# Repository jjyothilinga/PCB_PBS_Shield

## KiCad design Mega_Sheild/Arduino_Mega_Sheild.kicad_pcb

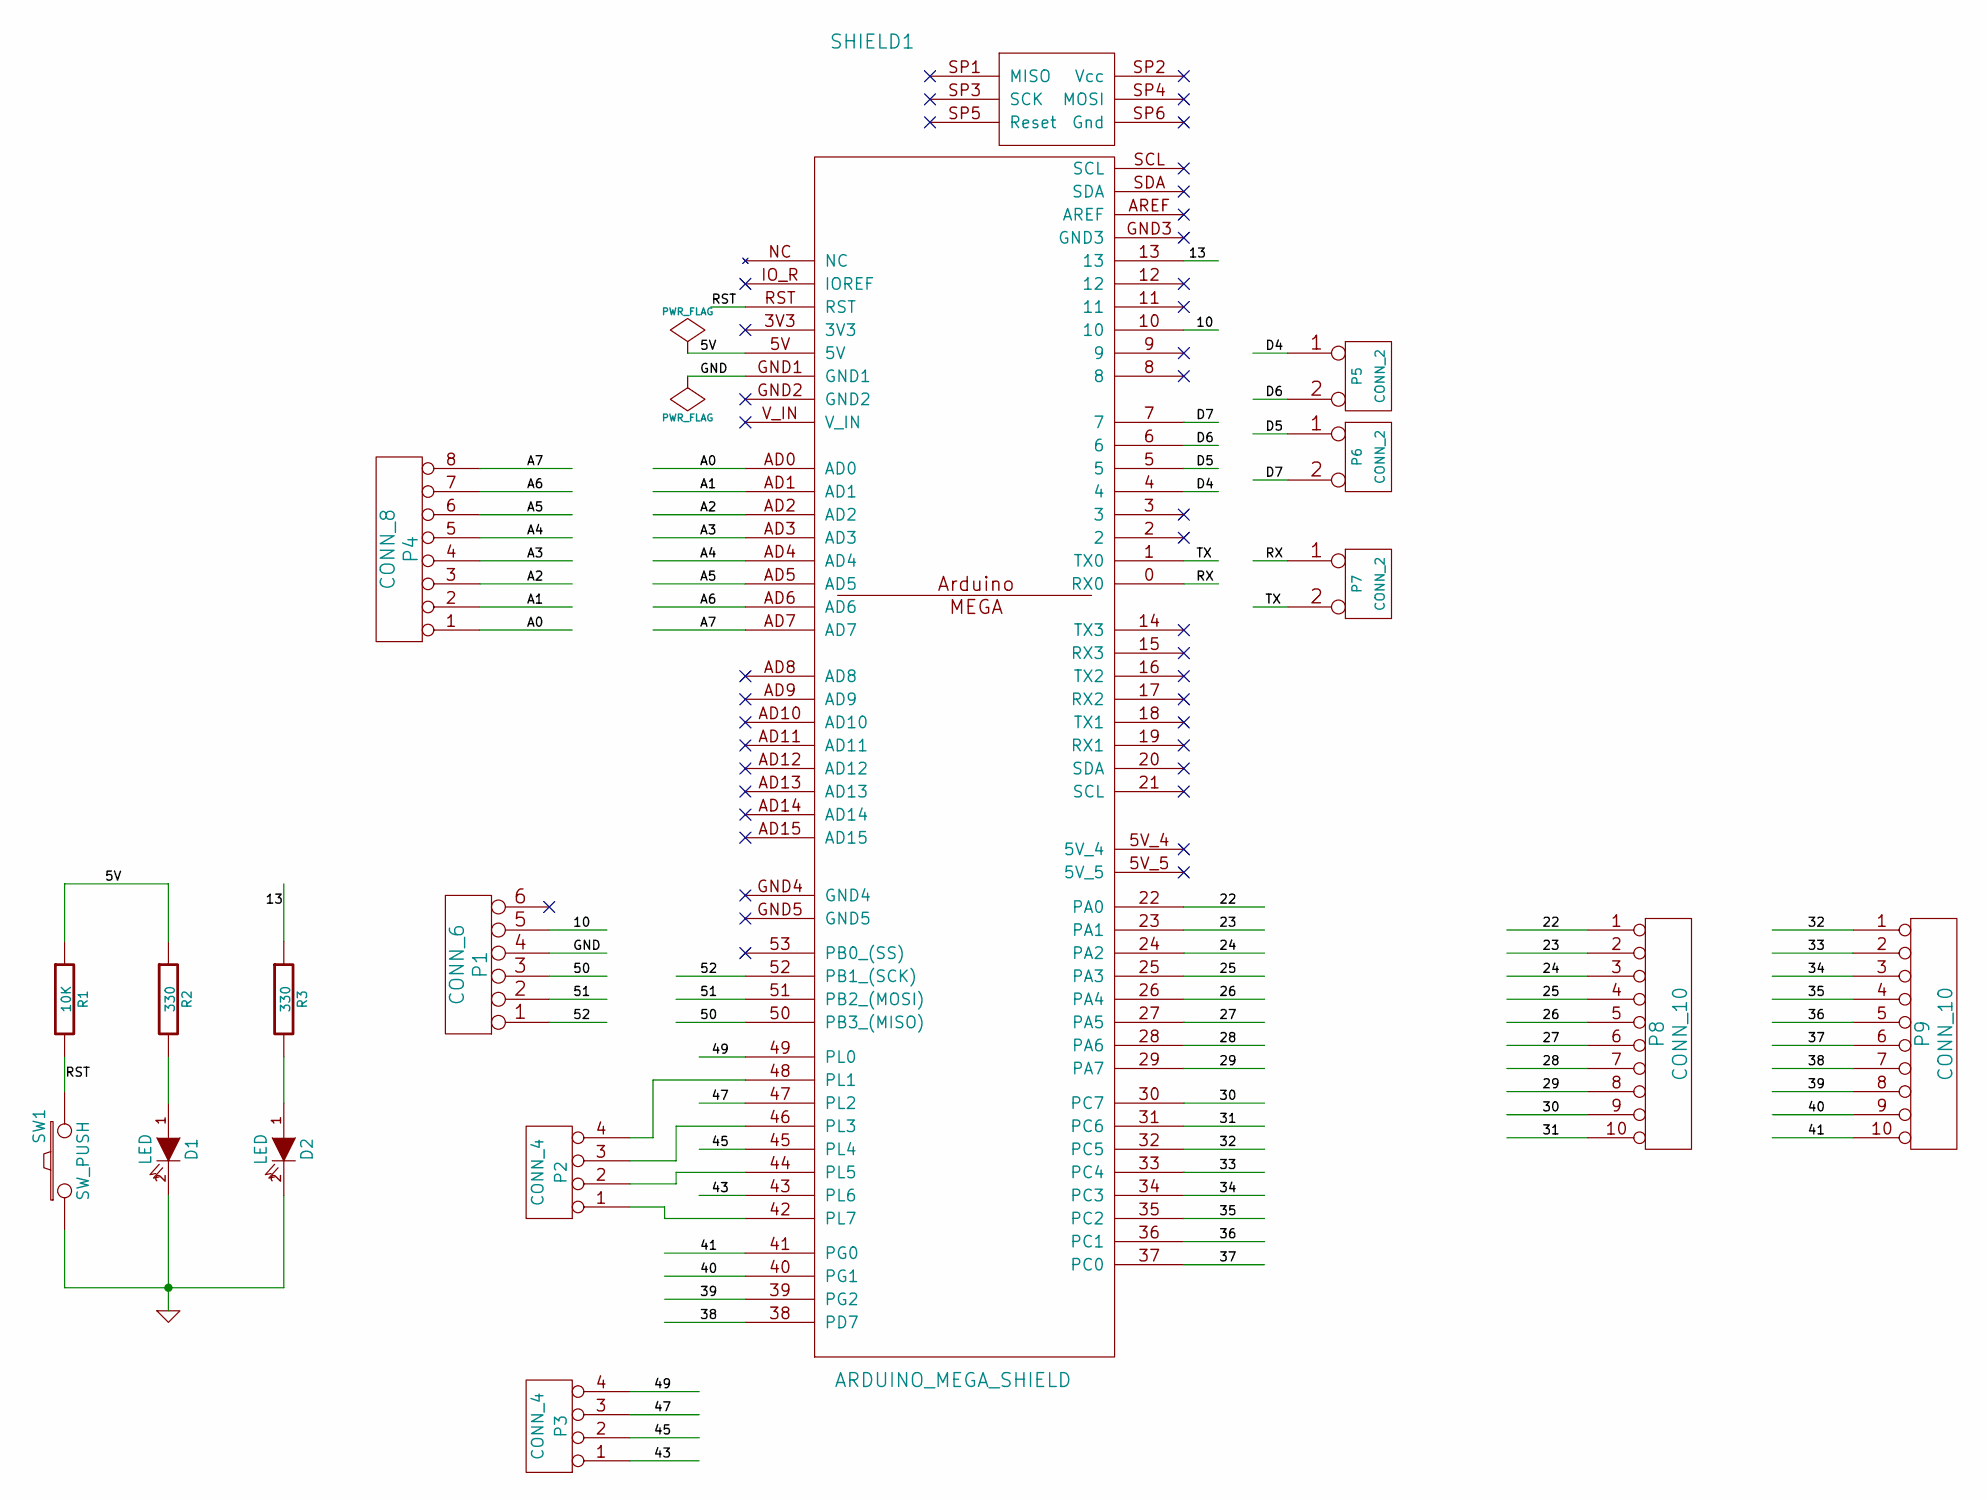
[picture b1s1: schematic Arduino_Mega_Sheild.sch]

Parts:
D1, D2: LED
P1: CONN_6
P2, P3: CONN_4
P4: CONN_8
P5, P6, P7: CONN_2
P8, P9: CONN_10
R1: 10K
R2, R3: 330
SHIELD1: ARDUINO_MEGA_SHIELD
SW1: SW_PUSH

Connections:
/5V: R1.1, R2.1, SHIELD1.5V
/10: P1.5, SHIELD1.10
/13: R3.1, SHIELD1.13
/22: P8.1, SHIELD1.22 (PA0)
/23: P8.2, SHIELD1.23 (PA1)
/24: P8.3, SHIELD1.24 (PA2)
/25: P8.4, SHIELD1.25 (PA3)
/26: P8.5, SHIELD1.26 (PA4)
/27: P8.6, SHIELD1.27 (PA5)
/28: P8.7, SHIELD1.28 (PA6)
/29: P8.8, SHIELD1.29 (PA7)
/30: P8.9, SHIELD1.30 (PC7)
/31: P8.10, SHIELD1.31 (PC6)
/32: P9.1, SHIELD1.32 (PC5)
/33: P9.2, SHIELD1.33 (PC4)
/34: P9.3, SHIELD1.34 (PC3)
/35: P9.4, SHIELD1.35 (PC2)
/36: P9.5, SHIELD1.36 (PC1)
/37: P9.6, SHIELD1.37 (PC0)
/38: P9.7, SHIELD1.38 (PD7)
/39: P9.8, SHIELD1.39 (PG2)
/40: P9.9, SHIELD1.40 (PG1)
/41: P9.10, SHIELD1.41 (PG0)
/43: P3.1, SHIELD1.43 (PL6)
/45: P3.2, SHIELD1.45 (PL4)
/47: P3.3, SHIELD1.47 (PL2)
/49: P3.4, SHIELD1.49 (PL0)
/50: P1.3, SHIELD1.50 (PB3_(MISO))
/51: P1.2, SHIELD1.51 (PB2_(MOSI))
/52: P1.1, SHIELD1.52 (PB1_(SCK))
/A0: P4.1, SHIELD1.AD0
/A1: P4.2, SHIELD1.AD1
/A2: P4.3, SHIELD1.AD2
/A3: P4.4, SHIELD1.AD3
/A4: P4.5, SHIELD1.AD4
/A5: P4.6, SHIELD1.AD5
/A6: P4.7, SHIELD1.AD6
/A7: P4.8, SHIELD1.AD7
/D4: P5.1, SHIELD1.4
/D5: P6.1, SHIELD1.5
/D6: P5.2 (PM), SHIELD1.6
/D7: P6.2 (PM), SHIELD1.7
/RST: R1.2, SHIELD1.RST, SW1.2
/RX: P7.1, SHIELD1.0 (RX0)
/TX: P7.2 (PM), SHIELD1.1 (TX0)
GND: D1.2 (K), D2.2 (K), P1.4, SHIELD1.GND1, SW1.1
unnamed: P2.4, SHIELD1.48 (PL1)
unnamed: P2.3, SHIELD1.46 (PL3)
unnamed: D2.1 (A), R3.2
unnamed: D1.1 (A), R2.2
unnamed: P2.2, SHIELD1.44 (PL5)
unnamed: P2.1, SHIELD1.42 (PL7)

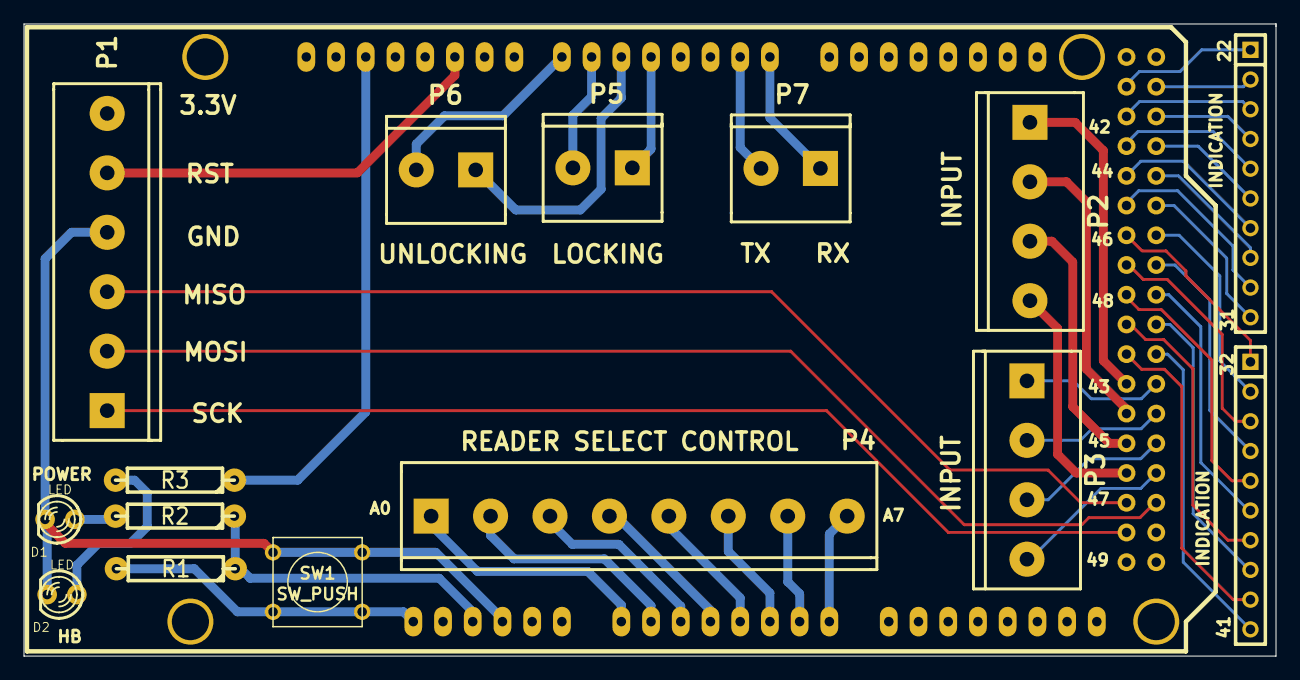
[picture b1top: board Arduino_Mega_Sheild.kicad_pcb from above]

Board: 2 copper layers, 107.0 x 54.0 mm, 16 parts (0 on the bottom side), 52 nets.

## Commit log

2016-02-15 :confetti_ball: Added .gitattributes & .gitignore files
2016-02-15 Completed
